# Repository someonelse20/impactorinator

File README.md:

# impactorinator
An impact bag that can measure the force of a punch or a kick.

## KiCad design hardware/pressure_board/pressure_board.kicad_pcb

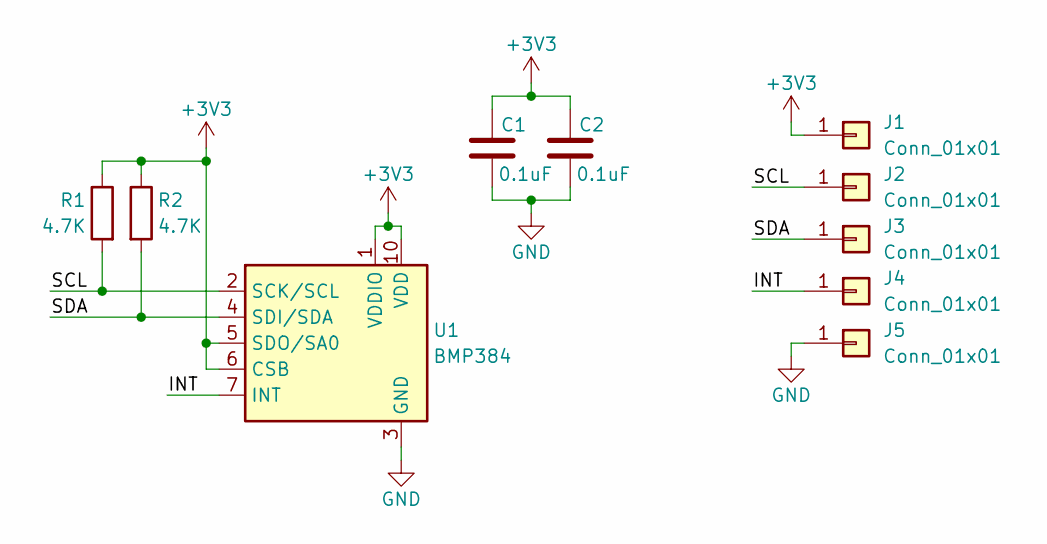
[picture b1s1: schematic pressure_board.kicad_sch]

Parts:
C1, C2: 0.1uF; C_0402_1005Metric; MPN GRM155R71H104KE14D
J1, J2, J3, J4, J5: Conn_01x01; SolderWirePad_1x01_SMD_1x2mm
R1, R2: 4.7K; R_0402_1005Metric_Pad0.72x0.64mm_HandSolder
U1: BMP384; ST_HLGA-10_2x2mm_P0.5mm_LayoutBorder3x2y; MPN BMP384

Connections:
+3V3: C1.1, C2.1, J1.1 (Pin_1_1), R1.1, R2.1, U1.1 (VDDIO), U1.5 (SDO/SA0), U1.6 (CSB), U1.10 (VDD)
/INT: J4.1 (Pin_1_1), U1.7 (INT)
/SCL: J2.1 (Pin_1_1), R1.2, U1.2 (SCK/SCL)
/SDA: J3.1 (Pin_1_1), R2.2, U1.4 (SDI/SDA)
GND: C1.2, C2.2, J5.1 (Pin_1_1), U1.3 (GND), U1.8 (GND), U1.9 (GND)

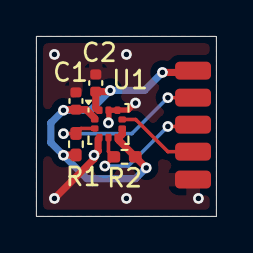
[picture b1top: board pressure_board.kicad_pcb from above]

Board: 2 copper layers, 10.0 x 10.0 mm, 10 parts (0 on the bottom side), 5 nets.
